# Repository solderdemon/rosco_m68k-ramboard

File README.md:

# rosco_m68k-ramboard

1–4 MB static RAM expansion for the [rosco_m68k](https://rosco-m68k.com) bus,
a maintained copy of Ross Bamford's **roscram-01** from
[rosco-m68k/hardware-projects](https://github.com/rosco-m68k/hardware-projects/tree/master/ram-expansion).
Eight AS6C4008 (512 K × 8) in DIP-32 sockets, a GAL16V8 address decoder (IC1),
three jumpers for the base address so several boards can coexist. The
schematic, logic and routing are the upstream design; this repository carries
the SolderDemon revision of the board file, kept in sync with the other
SolderDemon m68k cards.

## Changes against upstream

All changes are recorded as scripts in `tools/` and were applied in place to
`design/roscram01.kicad_pcb` with KiCad 10's Python. Re-running a script
changes nothing.

| Date | Script | Change |
|---|---|---|
| 2026-10-14 | `tools/migrate_100nf.py` | All nine 100 nF capacitors on the 5.08 mm radial footprint `SolderDemonCaps:C_Radial_5.08mm` (schematic, BOM and `fp-lib-table` follow). |
| 2026-10-14 | `tools/add_pin1_mark.py` | Filled silkscreen pointer plus `PIN 1` at pad 1 of the bus socket J1. |
| 2026-10-20 | `tools/align_capacitors.py` | Every 100 nF body on the centre line of its SRAM, C9 on the centre line of IC1, C10/C11 on that axis centred on the end pin rows of U1 and U2. The D0–D7 bend down to U1 (B.Cu) moved 1.7 mm right and D8/D9 led between the pads of C2 to make room; U2 pin 32 fed through its own via onto the bottom VCC run; the redundant F.Cu GND link from C1 to the J1 corner dropped (GND stays on both pours and the B.Cu run). Designators of the 100 nF parts inside the body outline. |
| 2026-10-20 | `tools/silk_notices.py` | Silkscreen: web link and OSHW logo removed, revision `r1`, copyright of both authors, `J1` beside `PIN 1` at 0.8 mm. |
| 2026-10-20 | `tools/resistor_refs.py` | Designators of R1–R5 inside the body outline, 1.0/0.15 mm along the body, as the SolderDemon cards print resistors. |

`design/CAMOutputs` holds the upstream Gerbers and drill files of the original
revision. They do **not** reflect the changes above; regenerate them before
ordering.

## Layout

```
design/      roscram01.kicad_pcb (KiCad 10), legacy roscram01.sch (KiCad 5 format),
             fp-lib-table, sym-lib-table, BOM (roscram01.csv), upstream CAMOutputs/
code/pld/    GAL16V8 address decoder: ic1_address_decoder.pld, JEDEC, burn.sh
tools/       the scripts above; tools/capacitors/ holds the 5.08 mm footprint
             library and the replacement helper they use
```

The `rosco_m68k` footprint library referenced by `fp-lib-table` is the
upstream library (`kicad-libs/rosco_m68k.pretty`, two directories up in the
original checkout). The board embeds every footprint, so it opens and checks
without it; KiCad only notes that the library is not available.

## Checks

```sh
K="/c/Program Files/KiCad/10.0/bin"
"$K/python.exe" tools/align_capacitors.py        # prints "already aligned"
"$K/kicad-cli.exe" pcb drc --severity-error --severity-warning -o capacitor-drc.rpt design/roscram01.kicad_pcb
```

Current state (`capacitor-drc.rpt`): 0 unconnected items, 63 findings, all of
them inherited from the upstream board and unchanged by the work here (short
leftover VCC stubs on B.Cu, IC1 silkscreen over its pads, three starved
thermals on SRAM GND pins, footprint-library notes). `baseline-capacitor-drc.rpt`
is the same check on the board before the capacitor migration, for comparison.

## Licence

Open-source hardware under the **CERN Open Hardware Licence v1.2**, see
[`LICENCE.hardware.txt`](LICENCE.hardware.txt). Copyright © 2020 Ross Bamford
and Contributors; modifications © 2026 SolderDemon. The upstream notices are
kept on the board and in the schematic title block, which also carries the
modification notice required by the licence.

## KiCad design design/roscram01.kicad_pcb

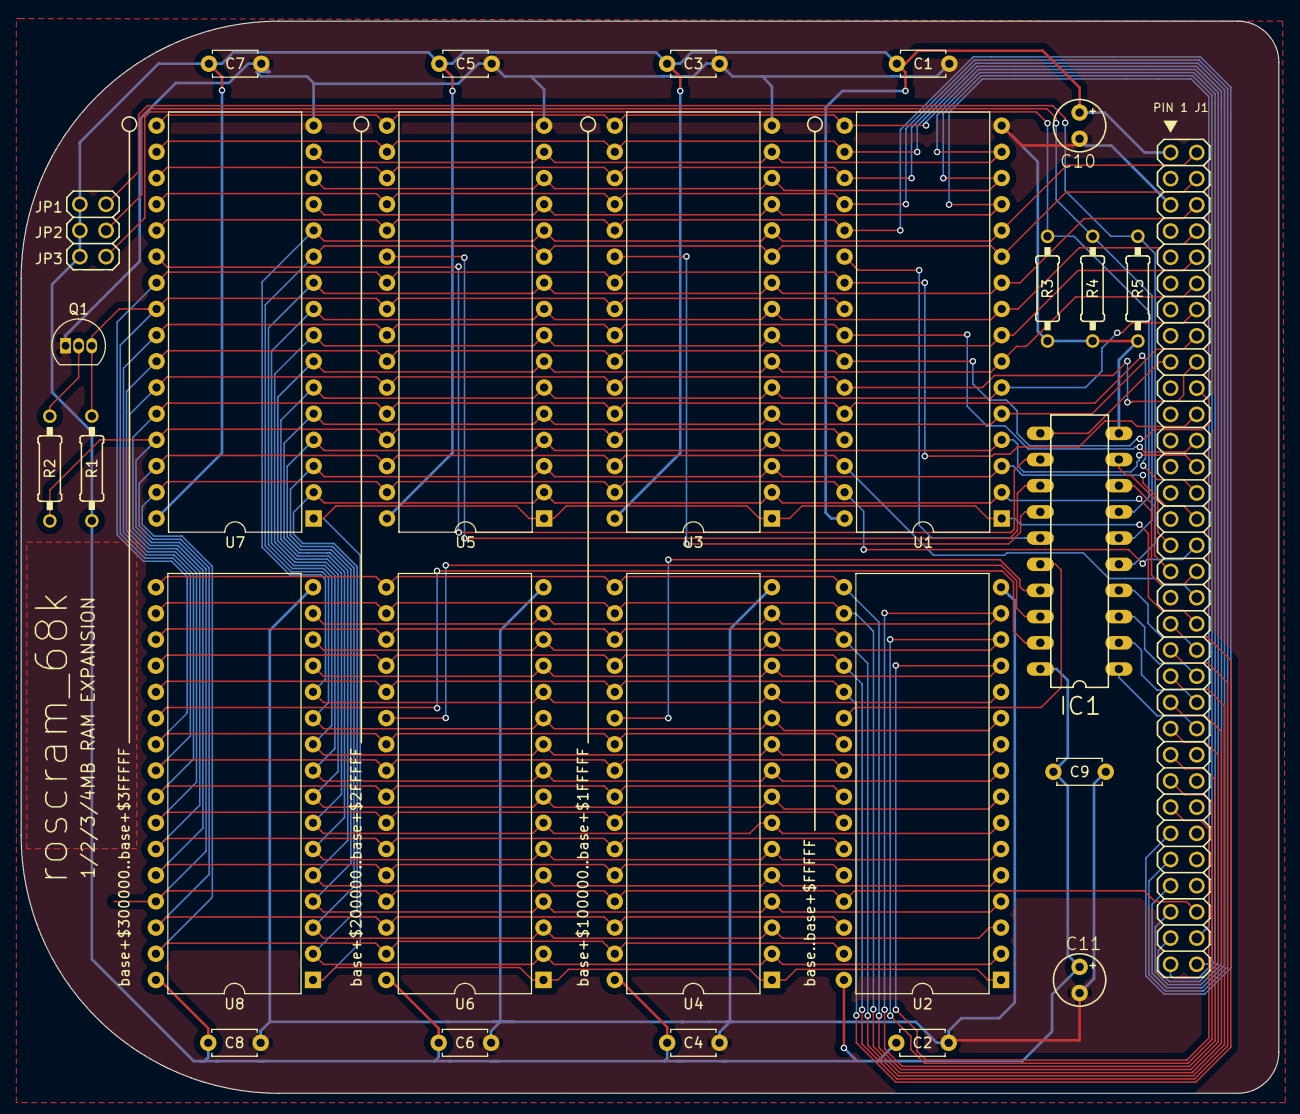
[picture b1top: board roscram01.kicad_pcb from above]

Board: 2 copper layers, 122.0 x 104.0 mm, 28 parts (0 on the bottom side), 58 nets.

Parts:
C1, C2, C3, C4, C5, C6, C7, C8, C9: 100nF; C_Radial_5.08mm
C10, C11: 100uF; C-Electolytic-2,5-5
IC1: ATF16V8VQL-15PU; DIL20
J1: Conn_02x32_Odd_Even; pin-2X32
JP1-3: Conn_02x03_Odd_Even; pin-2X3
Q1: 2N3904; TO-92_Inline
R1: 10K; R-0207_10
R2: 100K; R-0207_10
R3, R4, R5: 4K7; R-0207_10
U1, U2, U3, U4, U5, U6, U7, U8: AS6C4008-55PCN; DIP-32_W15.24mm

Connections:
A1: J1.2, U1.12, U2.12, U3.12, U4.12, U5.12, U6.12, U7.12, U8.12
A2: J1.4, U1.11, U2.11, U3.11, U4.11, U5.11, U6.11, U7.11, U8.11
A3: J1.6, U1.10, U2.10, U3.10, U4.10, U5.10, U6.10, U7.10, U8.10
A4: J1.8, U1.9, U2.9, U3.9, U4.9, U5.9, U6.9, U7.9, U8.9
A5: J1.10, U1.8, U2.8, U3.8, U4.8, U5.8, U6.8, U7.8, U8.8
A6: J1.12, U1.7, U2.7, U3.7, U4.7, U5.7, U6.7, U7.7, U8.7
A7: J1.14, U1.6, U2.6, U3.6, U4.6, U5.6, U6.6, U7.6, U8.6
A8: J1.16, U1.5, U2.5, U3.5, U4.5, U5.5, U6.5, U7.5, U8.5
A9: J1.18, U1.27, U2.27, U3.27, U4.27, U5.27, U6.27, U7.27, U8.27
A10: J1.20, U1.26, U2.26, U3.26, U4.26, U5.26, U6.26, U7.26, U8.26
A11: J1.22, U1.23, U2.23, U3.23, U4.23, U5.23, U6.23, U7.23, U8.23
A12: J1.24, U1.25, U2.25, U3.25, U4.25, U5.25, U6.25, U7.25, U8.25
A13: J1.26, U1.4, U2.4, U3.4, U4.4, U5.4, U6.4, U7.4, U8.4
A14: J1.28, U1.28, U2.28, U3.28, U4.28, U5.28, U6.28, U7.28, U8.28
A15: J1.30, U1.3, U2.3, U3.3, U4.3, U5.3, U6.3, U7.3, U8.3
A16: J1.32, U1.31, U2.31, U3.31, U4.31, U5.31, U6.31, U7.31, U8.31
A17: J1.34, U1.2, U2.2, U3.2, U4.2, U5.2, U6.2, U7.2, U8.2
A18: J1.36, U1.30, U2.30, U3.30, U4.30, U5.30, U6.30, U7.30, U8.30
A19: J1.38, U1.1, U2.1, U3.1, U4.1, U5.1, U6.1, U7.1, U8.1
A20: IC1.4, J1.40
A21: IC1.3, J1.42
A22: IC1.2, J1.44
A23: IC1.1, J1.46
D0: J1.62, U1.13, U3.13, U5.13, U7.13
D1: J1.64, U1.14, U3.14, U5.14, U7.14
D2: J1.63, U1.15, U3.15, U5.15, U7.15
D3: J1.61, U1.17, U3.17, U5.17, U7.17
D4: J1.59, U1.18, U3.18, U5.18, U7.18
D5: J1.57, U1.19, U3.19, U5.19, U7.19
D6: J1.55, U1.20, U3.20, U5.20, U7.20
D7: J1.53, U1.21, U3.21, U5.21, U7.21
D8: J1.51, U2.13, U4.13, U6.13, U8.13
D9: J1.49, U2.14, U4.14, U6.14, U8.14
D10: J1.47, U2.15, U4.15, U6.15, U8.15
D11: J1.45, U2.17, U4.17, U6.17, U8.17
D12: J1.43, U2.18, U4.18, U6.18, U8.18
D13: J1.41, U2.19, U4.19, U6.19, U8.19
D14: J1.39, U2.20, U4.20, U6.20, U8.20
D15: J1.37, U2.21, U4.21, U6.21, U8.21
ERAM1: IC1.16, U2.22
ERAM2: IC1.17, U4.22
ERAM3: IC1.18, U6.22
ERAM4: IC1.19, U8.22
EXPSEL: IC1.11, J1.17
GND: C1.2, C2.2, C3.2, C4.2, C5.2, C6.2, C7.2, C8.2, C9.2, C10.2, C11.2, IC1.10, J1.5, Q1.1, R3.2, R4.2, R5.2, U1.16, U2.16, U3.16, U4.16, U5.16, U6.16, U7.16, U8.16
JP1: IC1.5, JP1-3.5, R5.1
JP2: IC1.6, JP1-3.3, R4.1
JP3: IC1.7, JP1-3.1, R3.1
LDS: IC1.9, J1.31
unnamed: Q1.2, R2.1
ORAM1: IC1.15, U1.22
ORAM2: IC1.14, U3.22
ORAM3: IC1.13, U5.22
ORAM4: IC1.12, U7.22
RnW: J1.60, R2.2, U1.29, U2.29, U3.29, U4.29, U5.29, U6.29, U7.29, U8.29
UDS: IC1.8, J1.33
VCC: C1.1, C2.1, C3.1, C4.1, C5.1, C6.1, C7.1, C8.1, C9.1, C10.1, C11.1, IC1.20, J1.1, JP1-3.2, JP1-3.4, JP1-3.6, R1.2, U1.32, U2.32, U3.32, U4.32, U5.32, U6.32, U7.32, U8.32
WnR: Q1.3, R1.1, U1.24, U2.24, U3.24, U4.24, U5.24, U6.24, U7.24, U8.24

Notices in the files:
design/roscram01.kicad_pcb:
© 2020 Ross Bamford & Contributors · © 2026 SolderDemon
